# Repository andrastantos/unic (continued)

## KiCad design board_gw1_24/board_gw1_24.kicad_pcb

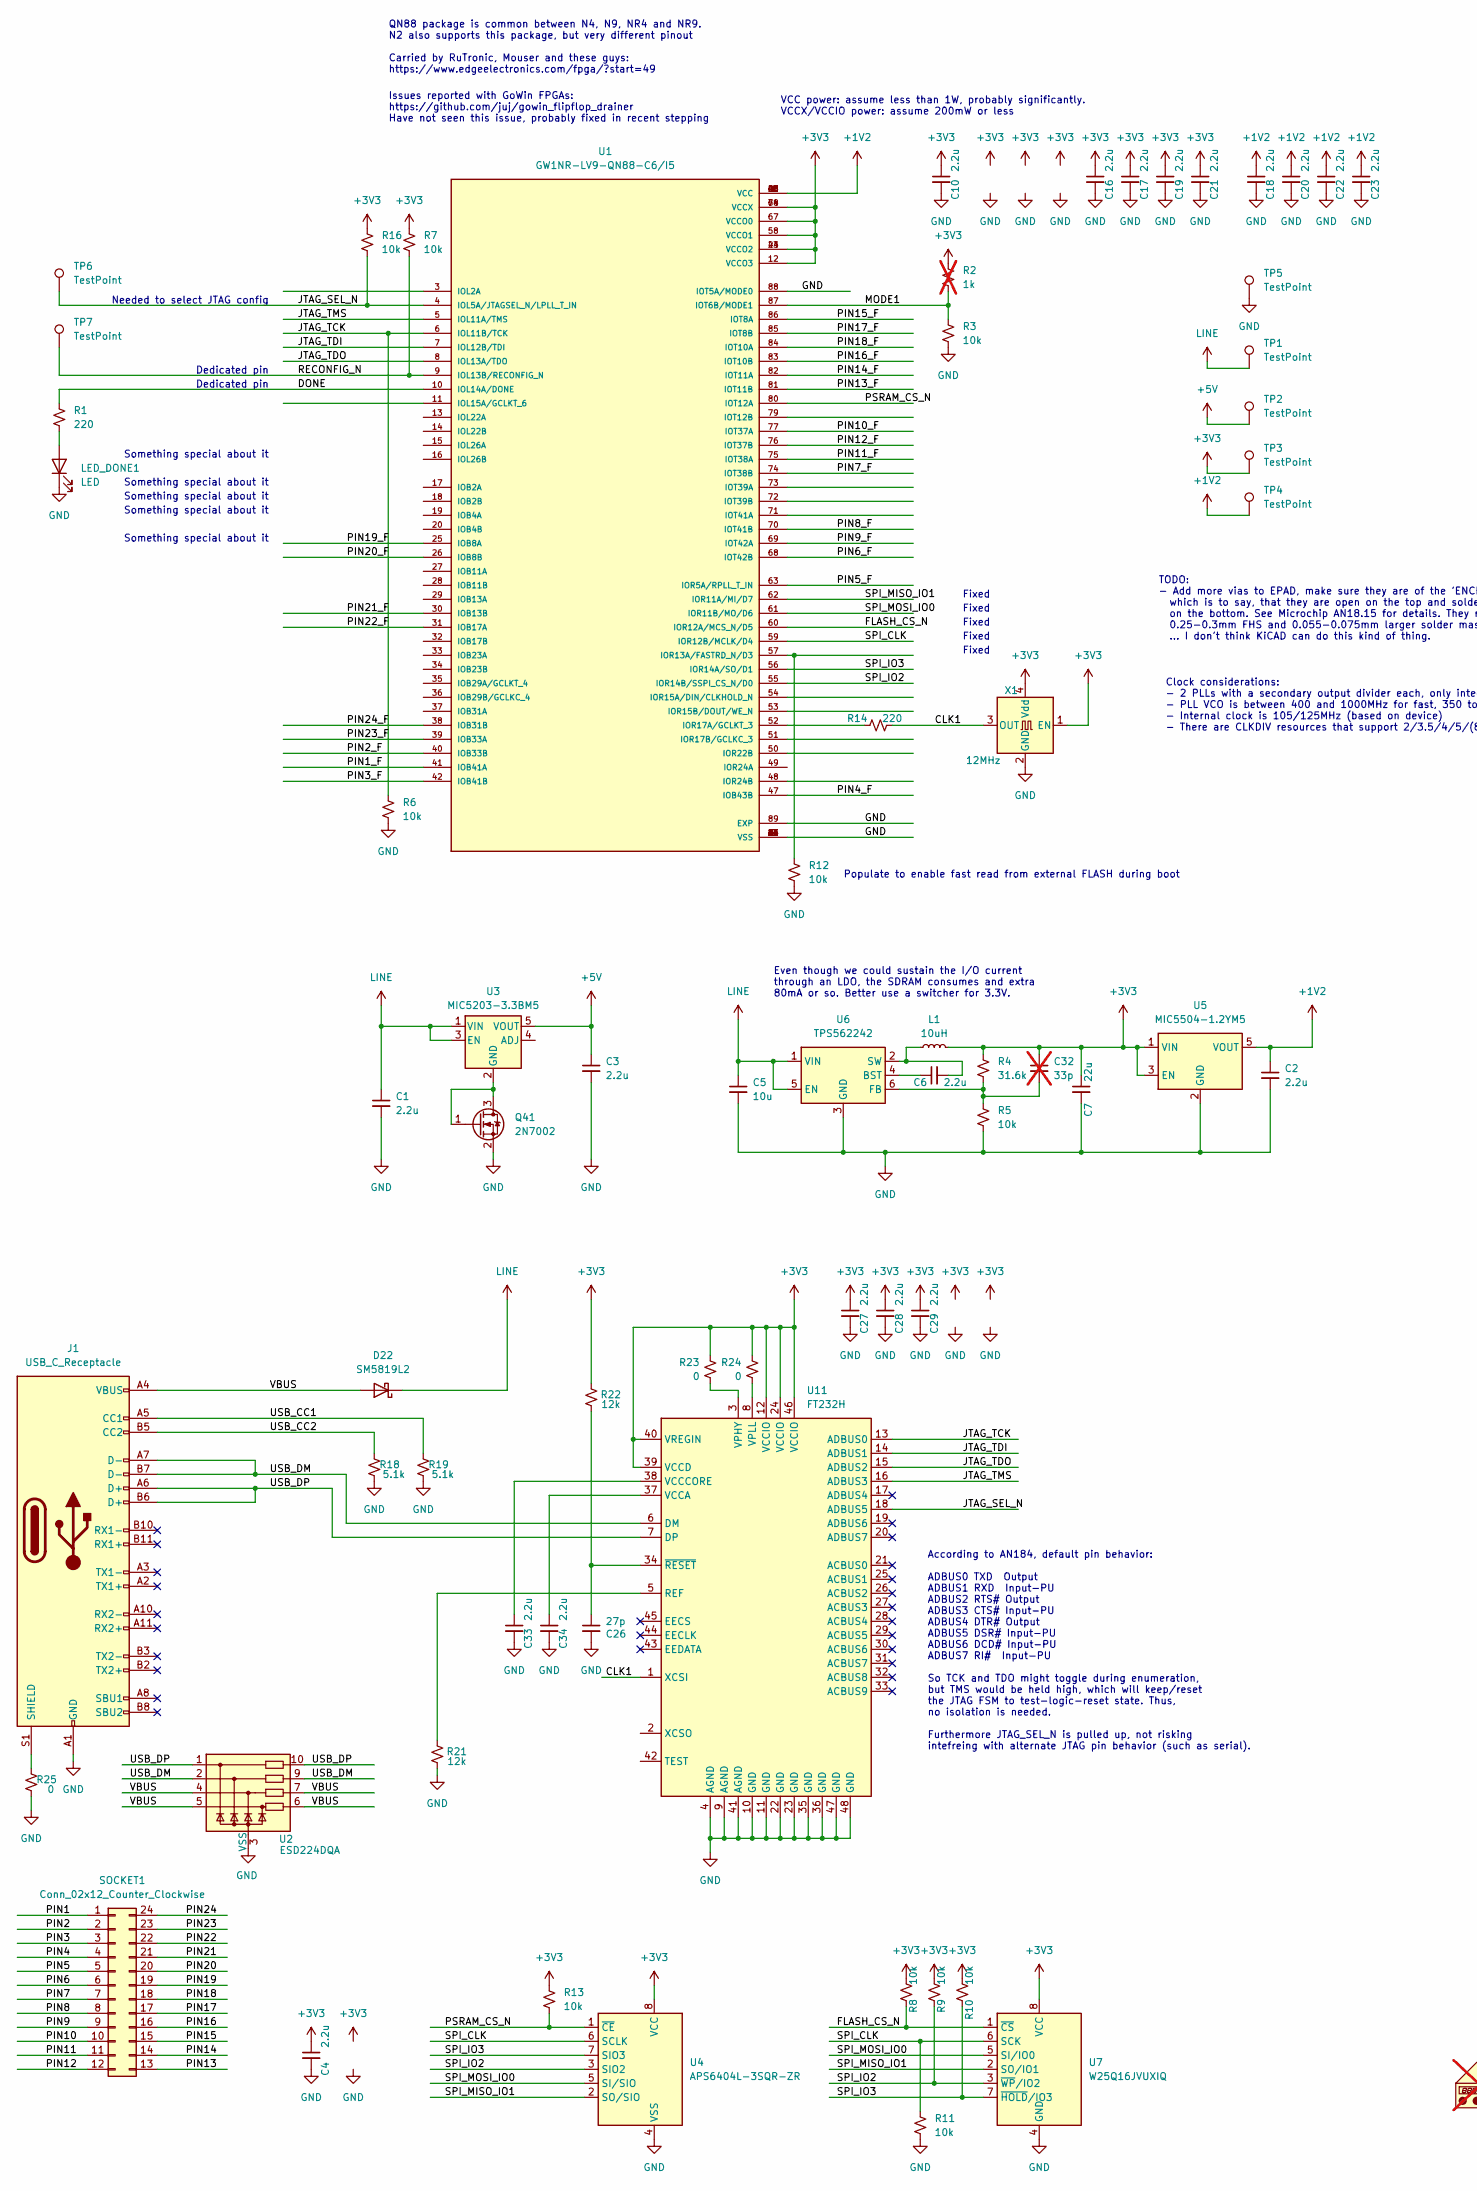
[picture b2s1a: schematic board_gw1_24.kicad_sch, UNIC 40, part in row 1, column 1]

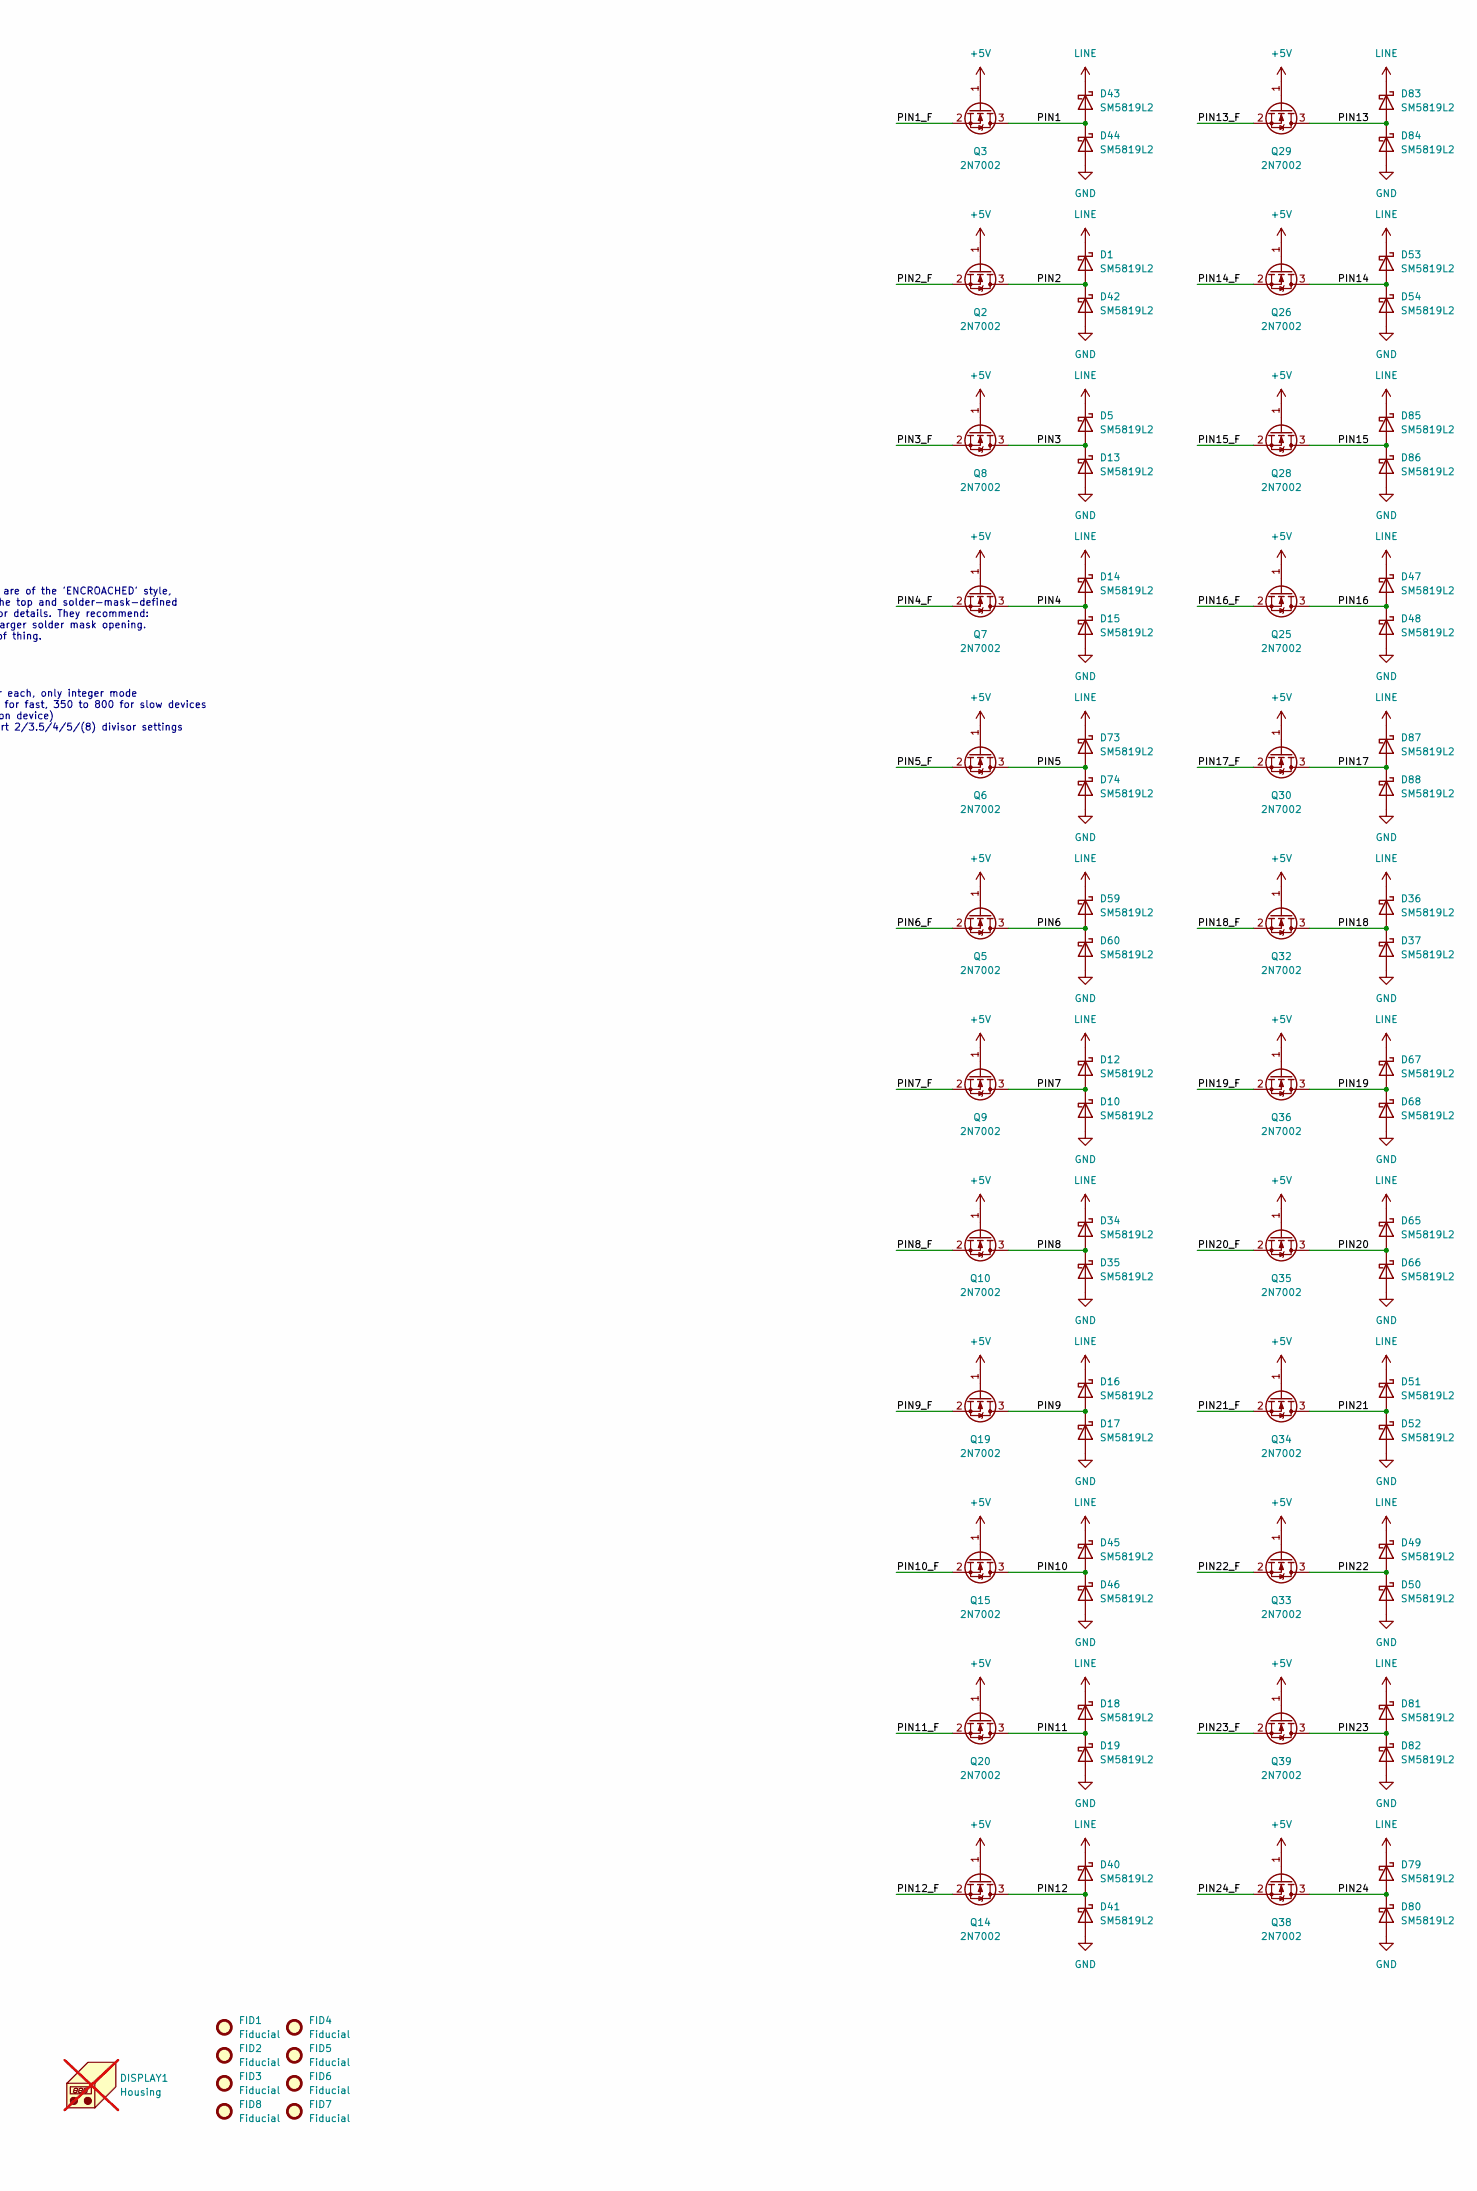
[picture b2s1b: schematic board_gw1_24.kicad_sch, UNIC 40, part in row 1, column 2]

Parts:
C1: 2.2u; C_0402_1005Metric_Pad0.74x0.62mm_HandSolder; mpn CC0402MRX5R6BB225
C2, C3, C4, C6, C10, C16, C17, C18, C19, C20, C21, C22, C23, C27, C28, C29, C33, C34: 2.2u; C_0201_0603Metric; mpn CC0402MRX5R6BB225
C5: 10u; C_0805_2012Metric_Pad1.18x1.45mm_HandSolder; mpn CL21A106KAYNNNG
C7: 22u; C_0805_2012Metric_Pad1.18x1.45mm_HandSolder; mpn CL21A226MQQNNNE
C26: 27p; C_0201_0603Metric
C32: 33p; C_0201_0603Metric; mpn CC0402MRX5R6BB225; not fitted
D1, D5, D10, D12, D13, D14, D15, D16, D17, D18, D19, D22, D34, D35, D36, D37, D40, D41, D42, D43, D44, D45, D46, D47, D48, D49, D50, D51, D52, D53, D54, D59, D60, D65, D66, D67, D68, D73, D74, D79, D80, D81, D82, D83, D84, D85, D86, D87, D88: SM5819L2; D_SOD-882
DISPLAY1: Housing; CFAL12832C-0091B-W_A; mpn CFAL12832C-0091B-W_A; not fitted
FID1, FID2, FID3, FID4, FID5, FID6, FID7, FID8: Fiducial; Fiducial_0.5mm_Mask1mm
J1: USB_C_Receptacle; USB_C_Receptacle_GCT_USB4115-03-C
L1: 10uH; L_1008_2520Metric_Pad1.43x2.20mm_HandSolder; mpn UHP 252012BF-100M
LED_DONE1: LED; LED_0402_1005Metric_Pad0.77x0.64mm_HandSolder; mpn CS42C-QL4
Q2, Q3, Q5, Q6, Q7, Q8, Q9, Q10, Q14, Q15, Q19, Q20, Q25, Q26, Q28, Q29, Q30, Q32, Q33, Q34, Q35, Q36, Q38, Q39, Q41: 2N7002; SOT-883; mpn 2N7002KL3A-TP
R1: 220; R_0201_0603Metric; mpn CR0402-JW-221GLF
R2: 1k; R_0201_0603Metric; mpn CR0402-JW-102GLF; not fitted
R3, R5, R6, R7, R8, R9, R10, R11, R12, R13, R16: 10k; R_0201_0603Metric; mpn CR0402-FX-1002GLF
R4: 31.6k; R_0201_0603Metric; mpn CR0402-FX-3162GLF
R14: 220; R_0201_0603Metric
R18, R19: 5.1k; R_0201_0603Metric
R21, R22: 12k; R_0201_0603Metric
R23, R24, R25: 0; R_0201_0603Metric
SOCKET1: Conn_02x12_Counter_Clockwise; DIP-24_pin_header; mpn BA3760-TUBL-4A-F5
TP1, TP2, TP3, TP4, TP5, TP6, TP7: TestPoint; TestPoint_Pad_D1.0mm
U1: GW1NR-LV9-QN88-C6/I5; QFN40P1000X1000X95-89N; PARTREV UG103-2.3E
U2: ESD224DQA; Diodes_UDFN-10_1.0x2.5mm_P0.5mm; mpn TVU1240R1ADG
U3: MIC5203-3.3BM5; SOT-23-5; mpn MIC5203-3.3YM5-TR
U4: APS6404L-3SQR-ZR; W25Q16JVUXIQ_TR; mpn APS6404L-3SQR-ZR
U5: MIC5504-1.2YM5; SOT-23-5; mpn MIC5504-1.2YM5-TR
U6: TPS562242; SOT-563; mpn TPS562242
U7: W25Q16JVUXIQ; W25Q16JVUXIQ_TR; mpn W25Q16JVUXIQ TR
U11: FT232H; LQFP-48_7x7mm_P0.5mm
X1: 12MHz; Oscillator_SMD_2.5x2.0mm; mpn SG-210STF 12.0000ML5

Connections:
+1V2: C2.1, C18.1, C20.1, C22.1, C23.1, TP4.1, U1.1 (VCC), U1.22 (VCC), U1.45 (VCC), U1.66 (VCC), U5.5 (VOUT)
+3V3: C4.1, C7.1, C10.1, C16.1, C17.1, C19.1, C21.1, C27.1, C28.1, C29.1, C32.1, L1.2, R2.1, R4.1, R7.1, R8.1, R9.1, R10.1, R13.1, R16.1, R22.2, R23.2, R24.2, TP3.1, U1.12 (VCCO3), U1.23 (VCCO2), U1.44 (VCCO2), U1.58 (VCCO1), U1.64 (VCCX), U1.67 (VCCO0), U1.78 (VCCX), U4.8 (VCC), U5.1 (VIN), U5.3 (EN), U7.8 (VCC), U11.12 (VCCIO), U11.24 (VCCIO), U11.39 (VCCD), U11.40 (VREGIN), U11.46 (VCCIO), X1.1 (EN), X1.4 (Vdd)
+5V: C3.1, Q2.1 (G), Q3.1 (G), Q5.1 (G), Q6.1 (G), Q7.1 (G), Q8.1 (G), Q9.1 (G), Q10.1 (G), Q14.1 (G), Q15.1 (G), Q19.1 (G), Q20.1 (G), Q25.1 (G), Q26.1 (G), Q28.1 (G), Q29.1 (G), Q30.1 (G), Q32.1 (G), Q33.1 (G), Q34.1 (G), Q35.1 (G), Q36.1 (G), Q38.1 (G), Q39.1 (G), TP2.1, U3.5 (VOUT)
/CLK1: R14.2, U11.1 (XCSI), X1.3 (OUT)
/DONE: R1.1, U1.10 (IOL14A/DONE)
/FLASH_CS_N: R8.2, U1.60 (IOR12A/MCS_N/D5), U7.1 (~CS)
/JTAG_SEL_N: R16.2, TP6.1, U1.4 (IOL5A/JTAGSEL_N/LPLL_T_IN), U11.18 (ADBUS5)
/JTAG_TCK: R6.1, U1.6 (IOL11B/TCK), U11.13 (ADBUS0)
/JTAG_TDI: U1.7 (IOL12B/TDI), U11.14 (ADBUS1)
/JTAG_TDO: U1.8 (IOL13A/TDO), U11.15 (ADBUS2)
/JTAG_TMS: U1.5 (IOL11A/TMS), U11.16 (ADBUS3)
/MODE1: R2.2, R3.1, U1.87 (IOT6B/MODE1)
/PIN1: D43.2 (A), D44.1 (K), Q3.3 (D), SOCKET1.1
/PIN1_F: Q3.2 (S), U1.41 (IOB41A)
/PIN2: D1.2 (A), D42.1 (K), Q2.3 (D), SOCKET1.2
/PIN2_F: Q2.2 (S), U1.40 (IOB33B)
/PIN3: D5.2 (A), D13.1 (K), Q8.3 (D), SOCKET1.3
/PIN3_F: Q8.2 (S), U1.42 (IOB41B)
/PIN4: D14.2 (A), D15.1 (K), Q7.3 (D), SOCKET1.4
/PIN4_F: Q7.2 (S), U1.47 (IOB43B)
/PIN5: D73.2 (A), D74.1 (K), Q6.3 (D), SOCKET1.5
/PIN5_F: Q6.2 (S), U1.63 (IOR5A/RPLL_T_IN)
/PIN6: D59.2 (A), D60.1 (K), Q5.3 (D), SOCKET1.6
/PIN6_F: Q5.2 (S), U1.68 (IOT42B)
/PIN7: D10.1 (K), D12.2 (A), Q9.3 (D), SOCKET1.7
/PIN7_F: Q9.2 (S), U1.74 (IOT38B)
/PIN8: D34.2 (A), D35.1 (K), Q10.3 (D), SOCKET1.8
/PIN8_F: Q10.2 (S), U1.70 (IOT41B)
/PIN9: D16.2 (A), D17.1 (K), Q19.3 (D), SOCKET1.9
/PIN9_F: Q19.2 (S), U1.69 (IOT42A)
/PIN10: D45.2 (A), D46.1 (K), Q15.3 (D), SOCKET1.10
/PIN10_F: Q15.2 (S), U1.77 (IOT37A)
/PIN11: D18.2 (A), D19.1 (K), Q20.3 (D), SOCKET1.11
/PIN11_F: Q20.2 (S), U1.75 (IOT38A)
/PIN12: D40.2 (A), D41.1 (K), Q14.3 (D), SOCKET1.12
/PIN12_F: Q14.2 (S), U1.76 (IOT37B)
/PIN13: D83.2 (A), D84.1 (K), Q29.3 (D), SOCKET1.13
/PIN13_F: Q29.2 (S), U1.81 (IOT11B)
/PIN14: D53.2 (A), D54.1 (K), Q26.3 (D), SOCKET1.14
/PIN14_F: Q26.2 (S), U1.82 (IOT11A)
/PIN15: D85.2 (A), D86.1 (K), Q28.3 (D), SOCKET1.15
/PIN15_F: Q28.2 (S), U1.86 (IOT8A)
/PIN16: D47.2 (A), D48.1 (K), Q25.3 (D), SOCKET1.16
/PIN16_F: Q25.2 (S), U1.83 (IOT10B)
/PIN17: D87.2 (A), D88.1 (K), Q30.3 (D), SOCKET1.17
/PIN17_F: Q30.2 (S), U1.85 (IOT8B)
/PIN18: D36.2 (A), D37.1 (K), Q32.3 (D), SOCKET1.18
/PIN18_F: Q32.2 (S), U1.84 (IOT10A)
/PIN19: D67.2 (A), D68.1 (K), Q36.3 (D), SOCKET1.19
/PIN19_F: Q36.2 (S), U1.25 (IOB8A)
/PIN20: D65.2 (A), D66.1 (K), Q35.3 (D), SOCKET1.20
/PIN20_F: Q35.2 (S), U1.26 (IOB8B)
/PIN21: D51.2 (A), D52.1 (K), Q34.3 (D), SOCKET1.21
/PIN21_F: Q34.2 (S), U1.30 (IOB13B)
/PIN22: D49.2 (A), D50.1 (K), Q33.3 (D), SOCKET1.22
/PIN22_F: Q33.2 (S), U1.31 (IOB17A)
/PIN23: D81.2 (A), D82.1 (K), Q39.3 (D), SOCKET1.23
/PIN23_F: Q39.2 (S), U1.39 (IOB33A)
/PIN24: D79.2 (A), D80.1 (K), Q38.3 (D), SOCKET1.24
/PIN24_F: Q38.2 (S), U1.38 (IOB31B)
/PSRAM_CS_N: R13.2, U1.80 (IOT12A), U4.1 (~CE)
/RECONFIG_N: R7.2, TP7.1, U1.9 (IOL13B/RECONFIG_N)
/SPI_CLK: R11.1, U1.59 (IOR12B/MCLK/D4), U4.6 (SCLK), U7.6 (SCK)
/SPI_IO2: R9.2, U1.55 (IOR14B/SSPI_CS_N/D0), U4.3 (SIO2), U7.3 (~WP/IO2)
/SPI_IO3: R10.2, U1.56 (IOR14A/SO/D1), U4.7 (SIO3), U7.7 (~HOLD/IO3)
/SPI_MISO_IO1: U1.62 (IOR11A/MI/D7), U4.2 (SO/SIO), U7.2 (SO/IO1)
/SPI_MOSI_IO0: U1.61 (IOR11B/MO/D6), U4.5 (SI/SIO), U7.5 (SI/IO0)
/USB_CC1: J1.A5 (CC1), R19.2
/USB_CC2: J1.B5 (CC2), R18.2
/USB_DM: J1.A7 (D-), J1.B7 (D-), U2.2, U2.9, U11.6 (DM)
/USB_DP: J1.A6 (D+), J1.B6 (D+), U2.1, U2.10, U11.7 (DP)
/VBUS: D22.2 (A), J1.A4 (VBUS), J1.A9 (VBUS), J1.B4 (VBUS), J1.B9 (VBUS), U2.4, U2.5, U2.6, U2.7
GND: C1.2, C2.2, C3.2, C4.2, C5.2, C7.2, C10.2, C16.2, C17.2, C18.2, C19.2, C20.2, C21.2, C22.2, C23.2, C26.2, C27.2, C28.2, C29.2, C33.2, C34.2, D10.2 (A), D13.2 (A), D15.2 (A), D17.2 (A), D19.2 (A), D35.2 (A), D37.2 (A), D41.2 (A), D42.2 (A), D44.2 (A), D46.2 (A), D48.2 (A), D50.2 (A), D52.2 (A), D54.2 (A), D60.2 (A), D66.2 (A), D68.2 (A), D74.2 (A), D80.2 (A), D82.2 (A), D84.2 (A), D86.2 (A), D88.2 (A), J1.A1 (GND), J1.A12 (GND), J1.B1 (GND), J1.B12 (GND), LED_DONE1.1 (K), Q41.2 (S), R3.2, R5.2, R6.2, R11.2, R12.2, R18.1, R19.1, R21.1, R25.1, TP5.1, U1.2 (VSS), U1.21 (VSS), U1.24 (VSS), U1.43 (VSS), U1.46 (VSS), U1.65 (VSS), U1.88 (IOT5A/MODE0), U1.89 (EXP), U2.3 (VSS), U2.8 (VSS), U4.4 (VSS), U5.2 (GND), U6.3 (GND), U7.4 (GND), U11.4 (AGND), U11.9 (AGND), U11.10 (GND), U11.11 (GND), U11.22 (GND), U11.23 (GND), U11.35 (GND), U11.36 (GND), U11.41 (AGND), U11.47 (GND), U11.48 (GND), X1.2 (GND)
LINE: C1.1, C5.1, D1.1 (K), D5.1 (K), D12.1 (K), D14.1 (K), D16.1 (K), D18.1 (K), D22.1 (K), D34.1 (K), D36.1 (K), D40.1 (K), D43.1 (K), D45.1 (K), D47.1 (K), D49.1 (K), D51.1 (K), D53.1 (K), D59.1 (K), D65.1 (K), D67.1 (K), D73.1 (K), D79.1 (K), D81.1 (K), D83.1 (K), D85.1 (K), D87.1 (K), TP1.1, U3.1 (VIN), U3.3 (EN), U6.1 (VIN), U6.5 (EN)
unnamed: J1.S1 (SHIELD), R25.2
unnamed: LED_DONE1.2 (A), R1.2
unnamed: Q41.1 (G), Q41.3 (D), U3.2 (GND)
unnamed: R12.1, U1.57 (IOR13A/FASTRD_N/D3)
unnamed: R14.1, U1.52 (IOR17A/GCLKT_3)
unnamed: C6.1, U6.4 (BST)
unnamed: C32.2, R4.2, R5.1, U6.6 (FB)
unnamed: C6.2, L1.1, U6.2 (SW)
unnamed: R21.2, U11.5 (REF)
unnamed: C34.1, U11.37 (VCCA)
unnamed: C33.1, U11.38 (VCCCORE)
unnamed: R23.1, U11.3 (VPHY)
unnamed: R24.1, U11.8 (VPLL)
unnamed: C26.1, R22.1, U11.34 (~RESET)

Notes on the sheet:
Issues reported with GoWin FPGAs: https://github.com/juj/gowin_flipflop_drainer Have not seen this issue, probably fixed in recent stepping
Populate to enable fast read from external FLASH during boot
Fixed
Something special about it
TODO: - Add more vias to EPAD, make sure they are of the 'ENCROACHED' style, which is to say, that they are open on the top and solder-mask-defined on the bottom. See Microchip AN18.15 for details. They recommend: 0.25-0.3mm FHS and 0.055-0.075mm larger solder mask opening. ... I don't think KiCAD 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
VCC power: assume less than 1W, probably significantly. VCCX/VCCIO power: assume 200mW or less
Clock considerations: - 2 PLLs with a secondary output divider each, only integer mode - PLL VCO is between 400 and 1000MHz for fast, 350 to 800 for slow devices - Internal clock is 105/125MHz (based on device) - There are CLKDIV resources that support 2/3.5/4/5/(8) divisor settings
Even though we could sustain the I/O current through an LDO, the SDRAM consumes and extra 80mA or so. Better use a switcher for 3.3V.
Dedicated pin
Needed to select JTAG config
QN88 package is common between N4, N9, NR4 and NR9. N2 also supports this package, but very different pinout Carried by RuTronic, Mouser and these guys: https://www.edgeelectronics.com/fpga/?start=49
According to AN184, default pin behavior: ADBUS0 TXD Output ADBUS1 RXD Input-PU ADBUS2 RTS# Output ADBUS3 CTS# Input-PU ADBUS4 DTR# Output ADBUS5 DSR# Input-PU ADBUS6 DCD# Input-PU ADBUS7 RI# Input-PU So TCK and TDO might toggle during enumeration, but TMS would be held high, which will keep/reset 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

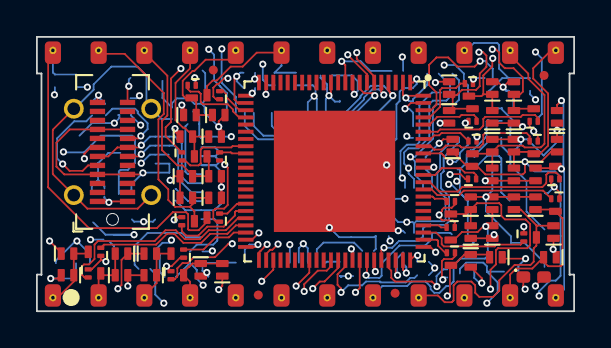
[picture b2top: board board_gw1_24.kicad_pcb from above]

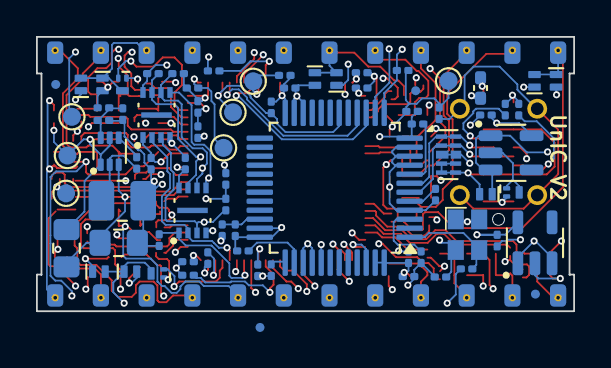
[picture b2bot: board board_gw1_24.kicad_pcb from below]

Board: 4 copper layers, 29.8 x 15.2 mm, 148 parts (77 on the bottom side), 88 nets.

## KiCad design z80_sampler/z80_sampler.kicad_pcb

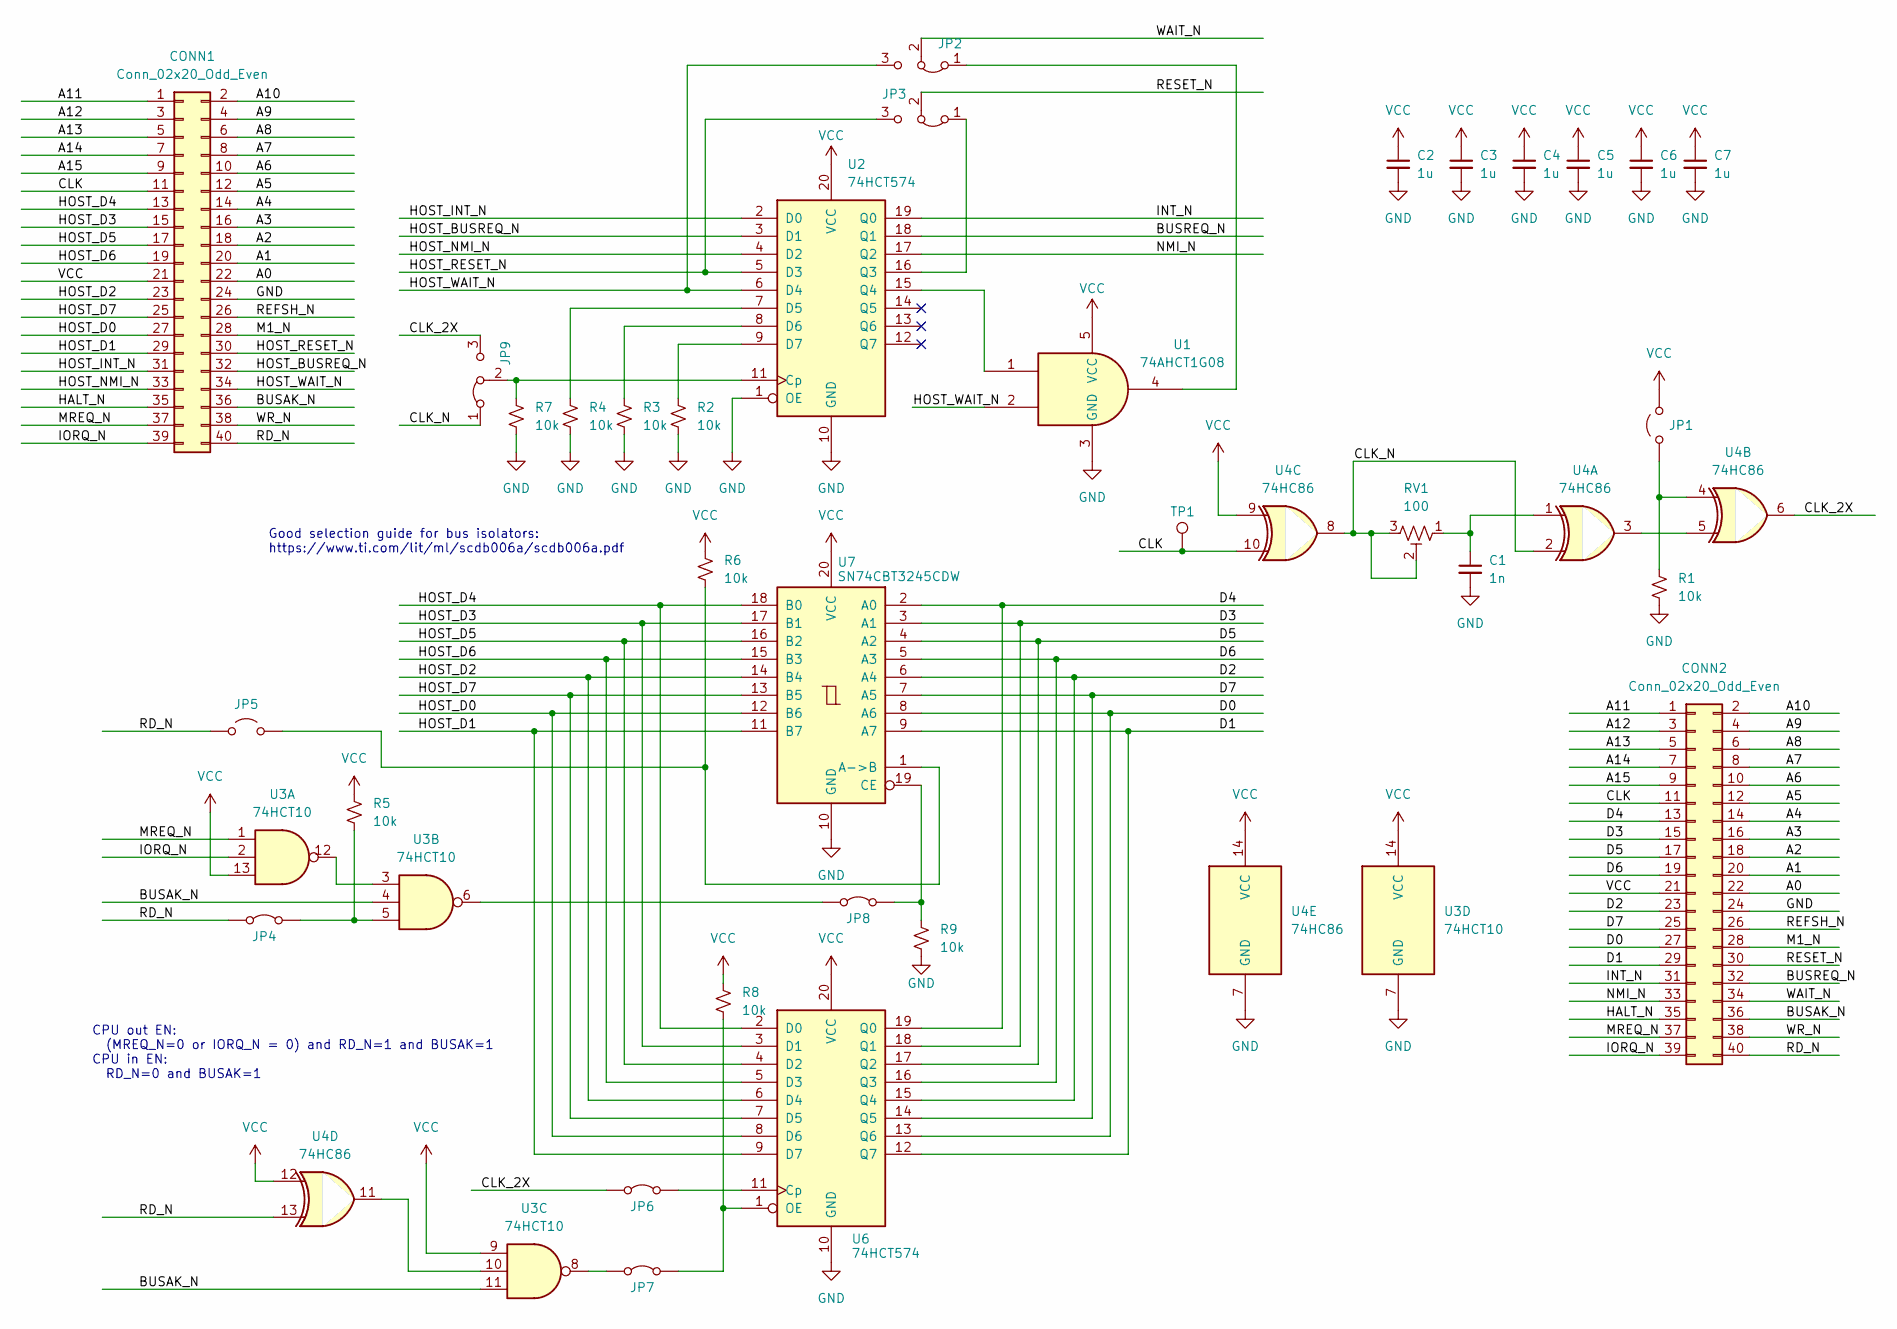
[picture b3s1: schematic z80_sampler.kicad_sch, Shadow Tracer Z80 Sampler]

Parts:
C1: 1n; C_0603_1608Metric_Pad1.08x0.95mm_HandSolder
C2, C3, C4, C5, C6, C7: 1u; C_0603_1608Metric_Pad1.08x0.95mm_HandSolder
CONN1: Conn_02x20_Odd_Even; PinSocket_2x20_P2.54mm_Horizontal
CONN2: Conn_02x20_Odd_Even; PinHeader_2x20_P2.54mm_Horizontal
JP1, JP5: Jumper_2_Open; PinHeader_1x02_P2.54mm_Vertical
JP2, JP3, JP9: Jumper_3_Bridged12; PinHeader_1x03_P2.54mm_Vertical
JP4, JP6, JP7, JP8: Jumper_2_Bridged; PinHeader_1x02_P2.54mm_Vertical
R1, R2, R3, R4, R5, R6, R7, R8, R9: 10k; R_0603_1608Metric_Pad0.98x0.95mm_HandSolder
RV1: 100; Potentiometer_Bourns_TC33X_Vertical; mpn TC33X-2-101E
TP1: TestPoint; PinHeader_1x01_P2.54mm_Vertical
U1: 74AHCT1G08; SOT-353_SC-70-5_Handsoldering
U2, U6: 74HCT574; SOIC-20W_7.5x12.8mm_P1.27mm
U3: 74HCT10; SOIC-14_3.9x8.7mm_P1.27mm
U4: 74HC86; SOIC-14_3.9x8.7mm_P1.27mm
U7: SN74CBT3245CDW; SOIC-20W_7.5x12.8mm_P1.27mm

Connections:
/A0: CONN1.22, CONN2.22
/A1: CONN1.20, CONN2.20
/A2: CONN1.18, CONN2.18
/A3: CONN1.16, CONN2.16
/A4: CONN1.14, CONN2.14
/A5: CONN1.12, CONN2.12
/A6: CONN1.10, CONN2.10
/A7: CONN1.8, CONN2.8
/A8: CONN1.6, CONN2.6
/A9: CONN1.4, CONN2.4
/A10: CONN1.2, CONN2.2
/A11: CONN1.1, CONN2.1
/A12: CONN1.3, CONN2.3
/A13: CONN1.5, CONN2.5
/A14: CONN1.7, CONN2.7
/A15: CONN1.9, CONN2.9
/BUSAK_N: CONN1.36, CONN2.36, U3.4, U3.11
/BUSREQ_N: CONN2.32, U2.18 (Q1)
/CLK: CONN1.11, CONN2.11, TP1.1, U4.10
/CLK_2X: JP6.1 (A), JP9.3 (B), U4.6
/CLK_N: JP9.1 (A), RV1.2, RV1.3, U4.2, U4.8
/D0: CONN2.27, U6.13 (Q6), U7.8 (A6)
/D1: CONN2.29, U6.12 (Q7), U7.9 (A7)
/D2: CONN2.23, U6.15 (Q4), U7.6 (A4)
/D3: CONN2.15, U6.18 (Q1), U7.3 (A1)
/D4: CONN2.13, U6.19 (Q0), U7.2 (A0)
/D5: CONN2.17, U6.17 (Q2), U7.4 (A2)
/D6: CONN2.19, U6.16 (Q3), U7.5 (A3)
/D7: CONN2.25, U6.14 (Q5), U7.7 (A5)
/HALT_N: CONN1.35, CONN2.35
/HOST_BUSREQ_N: CONN1.32, U2.3 (D1)
/HOST_D0: CONN1.27, U6.8 (D6), U7.12 (B6)
/HOST_D1: CONN1.29, U6.9 (D7), U7.11 (B7)
/HOST_D2: CONN1.23, U6.6 (D4), U7.14 (B4)
/HOST_D3: CONN1.15, U6.3 (D1), U7.17 (B1)
/HOST_D4: CONN1.13, U6.2 (D0), U7.18 (B0)
/HOST_D5: CONN1.17, U6.4 (D2), U7.16 (B2)
/HOST_D6: CONN1.19, U6.5 (D3), U7.15 (B3)
/HOST_D7: CONN1.25, U6.7 (D5), U7.13 (B5)
/HOST_INT_N: CONN1.31, U2.2 (D0)
/HOST_NMI_N: CONN1.33, U2.4 (D2)
/HOST_RESET_N: CONN1.30, JP3.3 (B), U2.5 (D3)
/HOST_WAIT_N: CONN1.34, JP2.3 (B), U1.2, U2.6 (D4)
/INT_N: CONN2.31, U2.19 (Q0)
/IORQ_N: CONN1.39, CONN2.39, U3.2
/M1_N: CONN1.28, CONN2.28
/MREQ_N: CONN1.37, CONN2.37, U3.1
/NMI_N: CONN2.33, U2.17 (Q2)
/RD_N: CONN1.40, CONN2.40, JP4.1 (A), JP5.1 (A), U4.13
/REFSH_N: CONN1.26, CONN2.26
/RESET_N: CONN2.30, JP3.2 (C)
/WAIT_N: CONN2.34, JP2.2 (C)
/WR_N: CONN1.38, CONN2.38
GND: C1.2, C2.2, C3.2, C4.2, C5.2, C6.2, C7.2, CONN1.24, CONN2.24, R1.2, R2.2, R3.2, R4.2, R7.2, R9.2, U1.3 (GND), U2.1 (OE), U2.10 (GND), U3.7 (GND), U4.7 (GND), U6.10 (GND), U7.10 (GND)
unnamed: C1.1, RV1.1, U4.1
unnamed: JP1.1 (A), R1.1, U4.4
unnamed: JP2.1 (A), U1.4
unnamed: JP3.1 (A), U2.16 (Q3)
unnamed: JP4.2 (B), R5.2, U3.5
unnamed: JP5.2 (B), R6.2, U7.1 (A->B)
unnamed: JP6.2 (B), U6.11 (Cp)
unnamed: JP7.1 (A), U3.8
unnamed: JP7.2 (B), R8.2, U6.1 (OE)
unnamed: JP8.1 (A), U3.6
unnamed: JP8.2 (B), R9.1, U7.19 (CE)
unnamed: JP9.2 (C), R7.1, U2.11 (Cp)
unnamed: R4.1, U2.7 (D5)
unnamed: R3.1, U2.8 (D6)
unnamed: R2.1, U2.9 (D7)
unnamed: U1.1, U2.15 (Q4)
unnamed: U3.10, U4.11
unnamed: U3.3, U3.12
unnamed: U4.3, U4.5
VCC: C2.1, C3.1, C4.1, C5.1, C6.1, C7.1, CONN1.21, CONN2.21, JP1.2 (B), R5.1, R6.1, R8.1, U1.5 (VCC), U2.20 (VCC), U3.9, U3.13, U3.14 (VCC), U4.9, U4.12, U4.14 (VCC), U6.20 (VCC), U7.20 (VCC)

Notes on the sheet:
Good selection guide for bus isolators: https://www.ti.com/lit/ml/scdb006a/scdb006a.pdf
CPU out EN: (MREQ_N=0 or IORQ_N = 0) and RD_N=1 and BUSAK=1 CPU in EN: RD_N=0 and BUSAK=1

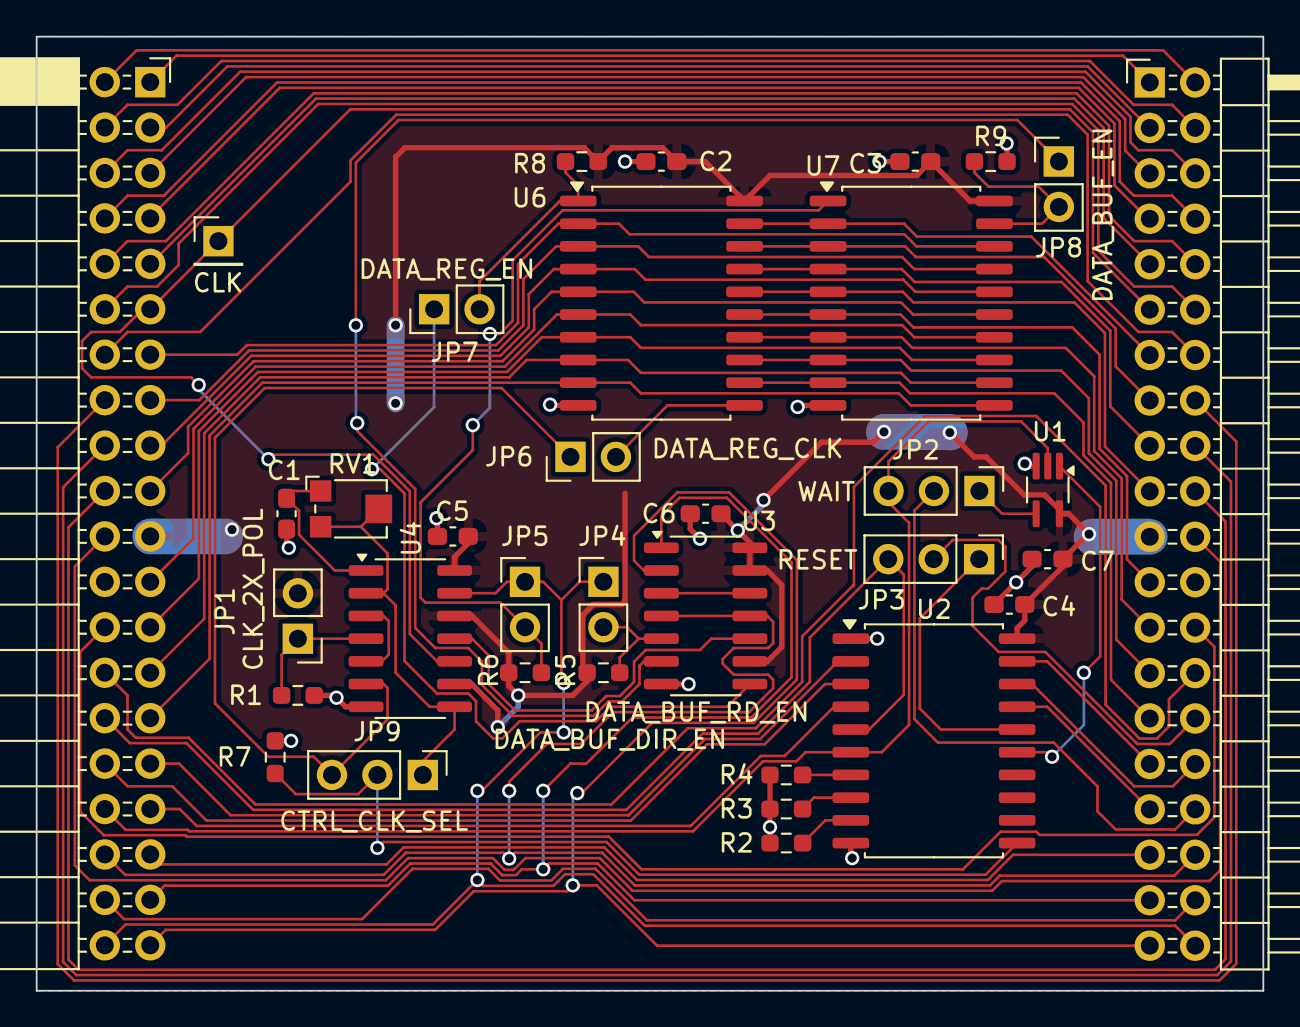
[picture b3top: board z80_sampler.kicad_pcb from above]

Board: 2 copper layers, 68.6 x 53.3 mm, 35 parts (0 on the bottom side), 74 nets.
